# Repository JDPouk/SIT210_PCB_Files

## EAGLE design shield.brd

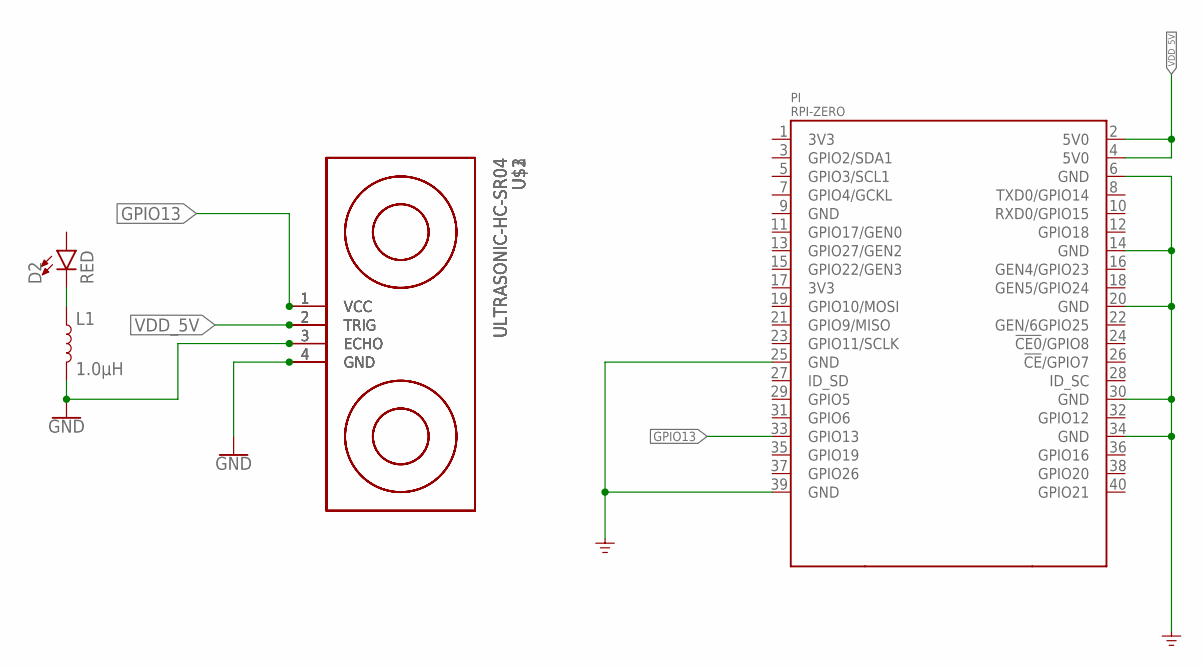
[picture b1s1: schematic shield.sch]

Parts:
D2: RED; LED-0603
L1: 1.0μH; 0805-WIDE
PI: RPI-ZERO; RASPBERRYPI_BASTELSTUBE_V13_RASPI_BOARD_B+_FULL
U$1, U$2, U$3: ULTRASONIC-HC-SR04

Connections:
GND: L1.2, PI.6 (GND), PI.14 (GND), PI.20 (GND), PI.25 (GND), PI.30 (GND), PI.34 (GND), PI.39 (GND), U$1.3 (ECHO), U$2.3 (ECHO), U$3.3 (ECHO)
GPIO13: PI.33 (GPIO13), U$1.1 (VCC), U$2.1 (VCC), U$3.1 (VCC)
unnamed: D2.C, L1.1
unnamed: U$1.4 (GND), U$2.4 (GND), U$3.4 (GND)
VDD_5V: PI.2 (5V0), PI.4 (5V0), U$1.2 (TRIG), U$2.2 (TRIG), U$3.2 (TRIG)

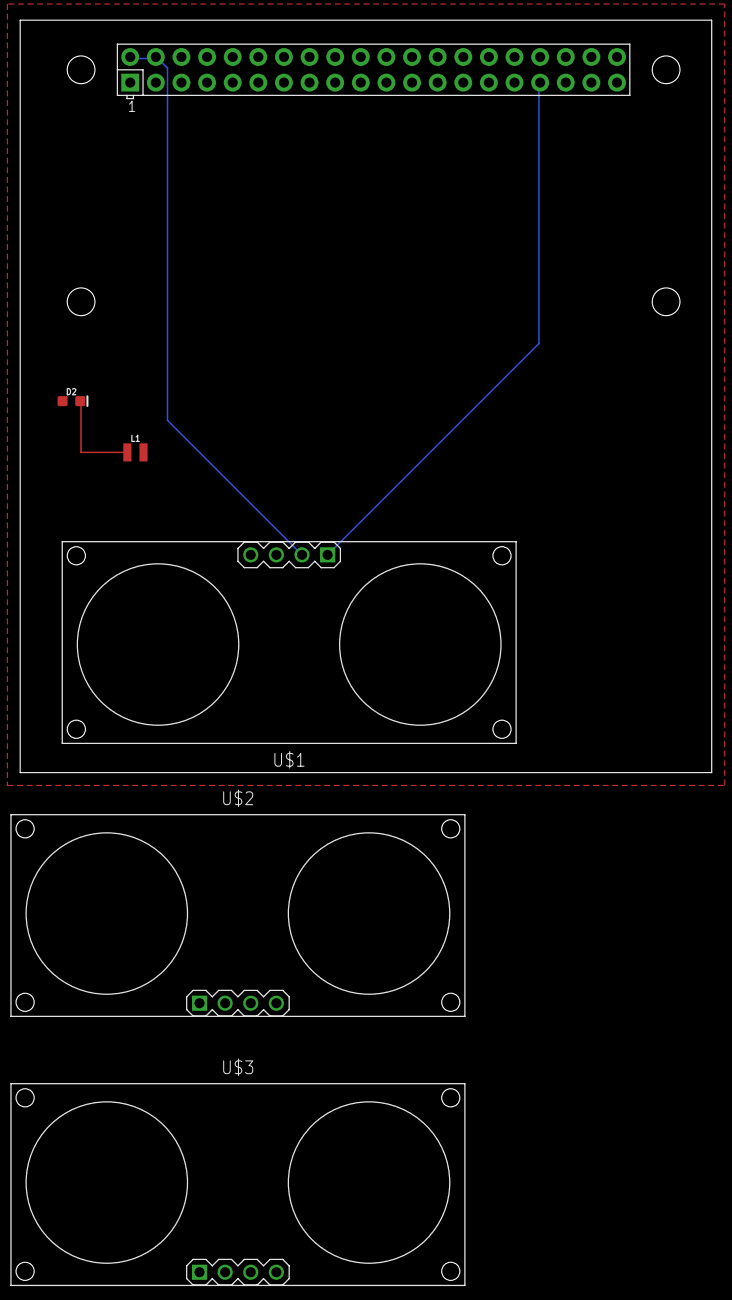
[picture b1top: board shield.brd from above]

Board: 2 copper layers, 68.6 x 74.6 mm, 6 parts (0 on the bottom side), 5 nets.

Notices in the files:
parts and their libraries:
SparkFun-LED: Licensing: Creative Commons ShareAlike 4.0 International - https://creativecommons.org/licenses/by-sa/4.0
diy-modules: Released under the Creative Commons Attribution 4.0 International License: http://creativecommons.org/licenses/by/4.0
